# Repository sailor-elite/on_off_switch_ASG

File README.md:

# ATTINY13A Automatic Stop And Go Off Switch

This project implements an automatic Stop and Go Off Switch for the AS&G (Auto Stop & Go) system in Mitsubishi ASX and Citroën C4 Aircross. The switch is designed to enhance user convenience by automatically disabling the AS&G system after ignition.

## Features

- **Automatic AS&G System Override**: Automatically disables the AS&G system after time defined by user.
- **Compact Design**: Designed with a small PCB footprint suitable for automotive integration.
- **Low Power Consumption**: Utilizes power-efficient components to minimize current draw.
- **Easy Installation**: Plug-and-play solution compatible with Mitsubishi ASX and Citroën C4 Aircross.

## Components

| Reference | Value         | Footprint                              |
|-----------|---------------|----------------------------------------|
| C1, C2    | 100nF/25V     | Capacitor_SMD:C_0603_1608Metric       |
| D1, D2    | 1N4007        | Diode_SMD:Nexperia_CFP3_SOD-123W      |
| K1        | HFD23_005-1ZS | relays:HFD230051ZS                    |
| Q1        | BC846         | Package_TO_SOT_SMD:SOT-23             |
| R1        | 1k            | Resistor_SMD:R_0805_2012Metric        |
| U1        | ATtiny13A-P   | Package_DIP:DIP-8_W7.62mm             |
| U2        | L78L05_SOT89  | Package_TO_SOT_SMD:SOT-89-3_Handsoldering |

## Dependencies
To compile and upload the code for the ATtiny13A, the following tools and libraries are required:
- AVR-GCC
- AVRDUDE
- Make
- USBasp Programmer
## Schematic

## PCB View

## Casing

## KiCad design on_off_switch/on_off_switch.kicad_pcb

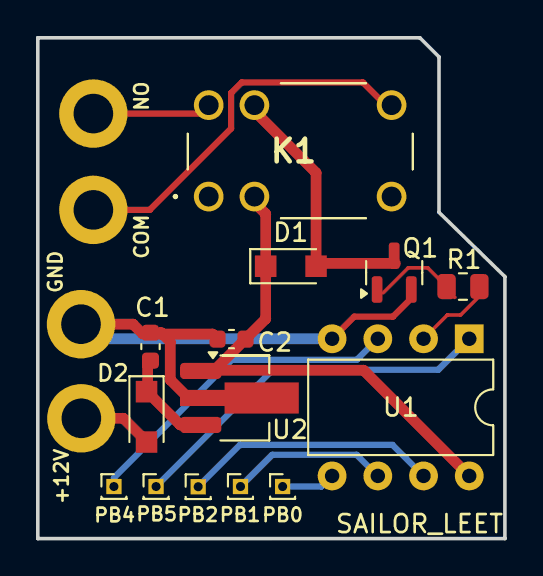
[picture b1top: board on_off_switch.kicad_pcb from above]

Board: 2 copper layers, 25.9 x 27.8 mm, 18 parts (0 on the bottom side), 14 nets.

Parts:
+12V: MountingHole_Pad_MP; MountingHole_2.2mm_M2_DIN965_Pad
C1, C2: 100nF/25V; C_0603_1608Metric
COM: MountingHole_Pad_MP; MountingHole_2.2mm_M2_DIN965_Pad
D1, D2: 1N4007; Nexperia_CFP3_SOD-123W
GND: MountingHole_Pad_MP; MountingHole_2.2mm_M2_DIN965_Pad
K1: HFD23_005-1ZS; HFD230051ZS
NO: MountingHole_Pad_MP; MountingHole_2.2mm_M2_DIN965_Pad
PB0, PB1, PB2, PB4, PB5: MountingHole_Pad_MP; PinHeader_1x01_P1.00mm_Vertical
Q1: BC846; SOT-23
R1: 1k; R_0805_2012Metric
U1: ATtiny13A-P; DIP-8_W7.62mm
U2: L78L05_SOT89; SOT-89-3_Handsoldering

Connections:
12VSIGNAL_PIN_AS&G: K1.6 (NO), NO.1
+5V: C2.1, D1.1 (K), K1.2 (COIL_1), U1.8 (VCC), U2.1 (OUT)
+12V: +12V.1, D2.2 (A)
GND: C1.2, C2.2, GND.1, Q1.2 (E), U1.4 (GND), U2.2 (GND)
MCU_PIN_AS&G: COM.1, K1.4 (COM_2)
unnamed: D1.2 (A), K1.5 (COIL_2), Q1.3 (C)
unnamed: C1.1, D2.1 (K), U2.3 (IN)
unnamed: Q1.1 (B), R1.2
unnamed: PB0.1, U1.5 (PB0)
unnamed: PB1.1, U1.6 (PB1)
unnamed: PB2.1, U1.7 (PB2)
unnamed: PB4.1, U1.3 (PB4)
unnamed: PB5.1, U1.1 (~RESET/PB5)
base_signal: R1.1, U1.2 (PB3)

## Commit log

2024-12-17 Added schematic design of PCB
2024-12-17 added PCB design
2024-12-17 Update README.md
    added PCB view
2024-12-19 Reworked schematics and PCB
    added mounting holes and renamed existing ones.
2024-12-19 Update README.md
    centered images
2024-12-19 Schematic and PCB change
    Added reverse polarity protection diode, replaced relay diode with 1n4007, removed mounting holes
2024-12-19 Update README.md
    changed components section
2024-12-19 Added Gerbers file, modified PCB design
    gerber and drill files, minor PCB changes
2025-01-19 Added source code + hex
2025-01-19 Added Casing
2025-02-28 Fix ATtiny13A issue with delay function
    Fix ATtiny13A issue by setting the correct fuse bits:
    - Change LFuse to 0x62 (disable clock division by 8 and disable CKOUT clock output)
    - Change HFuse to 0xFF (disable bootloader and Watchdog Timer)
